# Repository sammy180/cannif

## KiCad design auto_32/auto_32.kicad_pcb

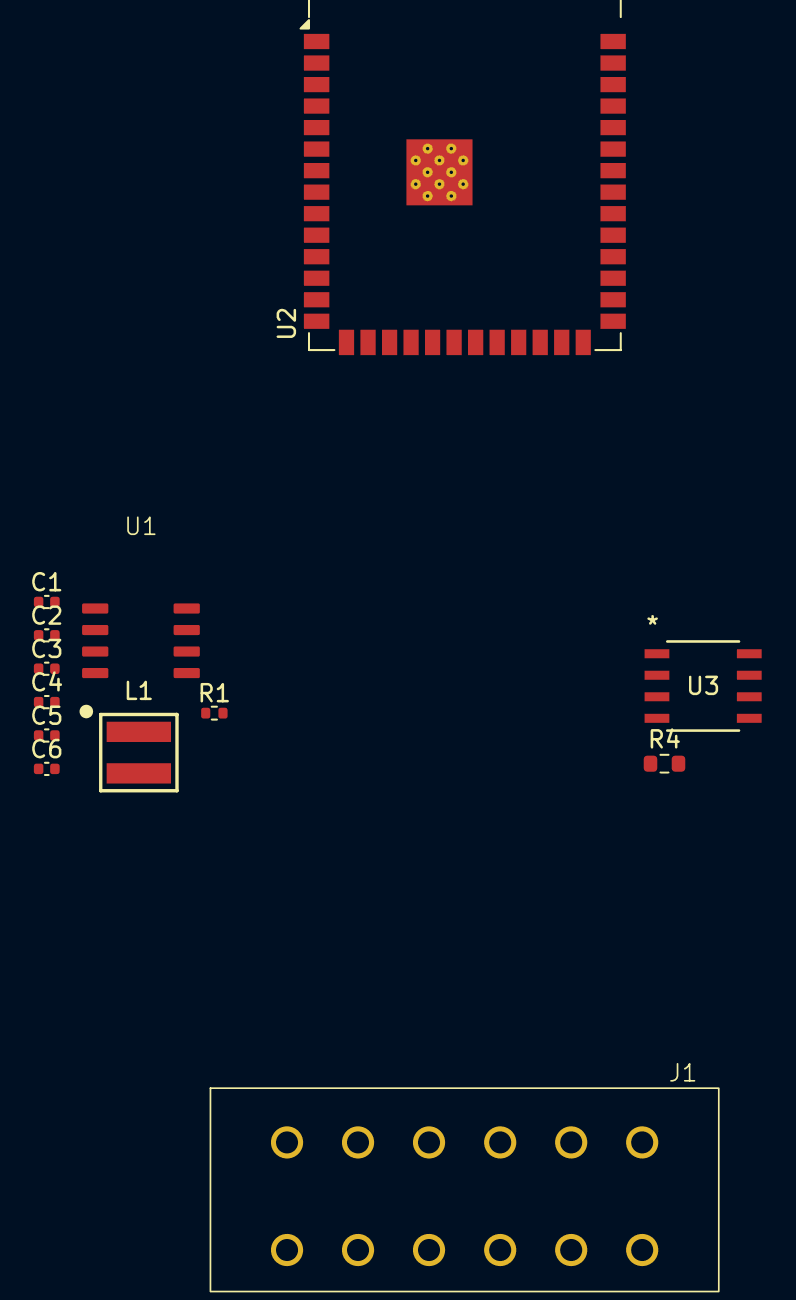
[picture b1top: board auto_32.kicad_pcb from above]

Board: 4 copper layers, 13 parts (0 on the bottom side), 11 nets, no tracks yet.

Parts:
C1, C2, C3, C4, C5, C6: C; C_0402_1005Metric
J1: DTM13-12PA-R008
L1: WE-XHMI_4040
R1: R; R_0402_1005Metric
R4: 0; R_0603_1608Metric
U1: SOIC_8
U2: ESP32-S3-WROOM-1
U3: TJA1051T/3/1J; SO8_SOT96-1_NXP

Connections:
/control/USB D-: R4.1, U2.13 (USB_D-)
unnamed: C3.1, R1.2
unnamed: C6.1, L1.2
unnamed: C5.1, U1.1 (BOOT)
unnamed: C2.1, R1.1, U1.6 (COMP)
unnamed: C1.2, C2.2, C3.2, C4.2, C6.2, U1.7 (GND)
unnamed: C5.2, L1.1, U1.8 (PH)
unnamed: C4.1, U1.4 (SS)
unnamed: U2.32 (IO39), U3.4 (RXD)
unnamed: U2.33 (IO40), U3.1 (TXD)
unnamed: U2.34 (IO41), U3.8 (S)

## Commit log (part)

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2026-01-30 chore: ignore node_modules
2026-01-30 clean commit
2026-02-02 peripheral schematic and reset button added
2026-02-02 peripheral schematic added
2026-02-03 hub , uart converter and usbc port added
2026-02-12 no comment see date
2026-02-20 mcu changed to rp2350
2026-02-26 esp wroom reintroduced and can phy layer chip added
2026-04-09 march update
2026-04-10 march lib update
